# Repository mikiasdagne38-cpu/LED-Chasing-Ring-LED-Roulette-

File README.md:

# LED-Chasing-Ring-LED-Roulette-
This circuit makes a ring of LEDs light up one by one in a fast circle, creating a "chasing" or running light effect. It is a classic hobbyist project used for decorative lights, games, or electronic roulette.

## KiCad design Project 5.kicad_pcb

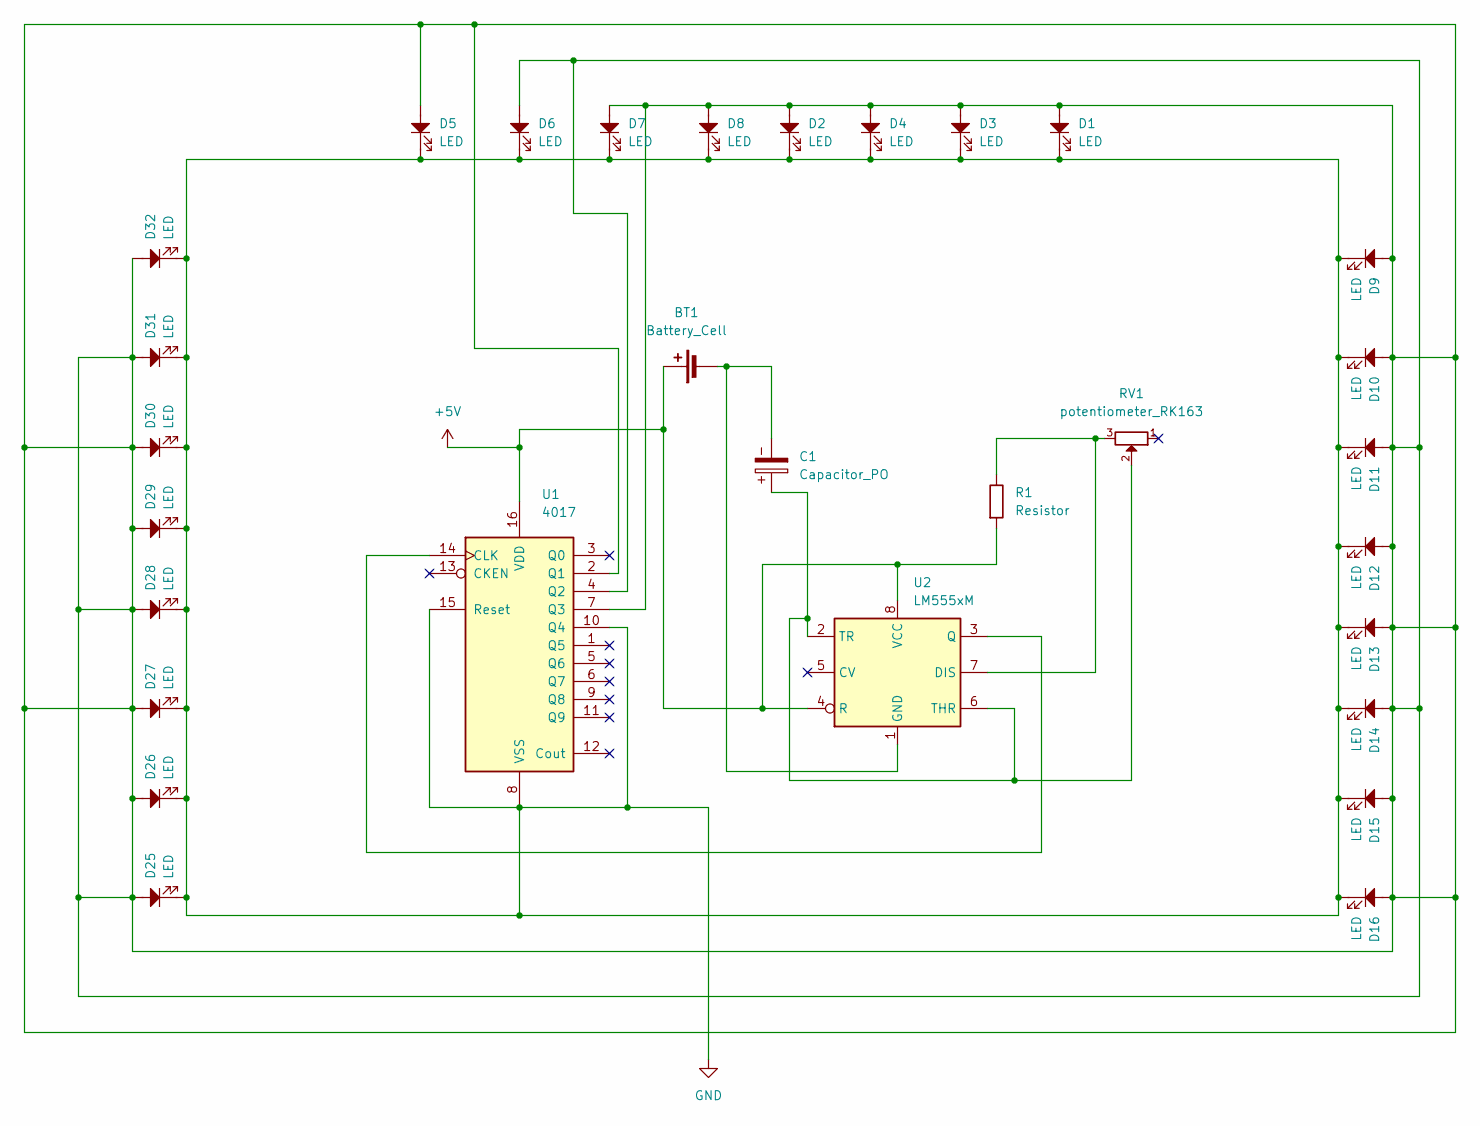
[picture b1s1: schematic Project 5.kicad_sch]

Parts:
BT1: Battery_Cell; TerminalBlock_Xinya_XY308-2.54-2P_1x02_P2.54mm_Horizontal
C1: Capacitor_PO; CP_Radial_D5.0mm_P2.50mm
D1, D2, D3, D4, D5, D6, D7, D8, D9, D10, D11, D12, D13, D14, D15, D16, D25, D26, D27, D28, D29, D30, D31, D32: LED; LED_D5.0mm
R1: Resistor; R_Axial_DIN0207_L6.3mm_D2.5mm_P10.16mm_Horizontal
RV1: potentiometer_RK163; TRIM_3296W-1-250
U1: 4017; DIP794W45P254L1969H508Q16
U2: LM555xM; SOIC-8_3.9x4.9mm_P1.27mm

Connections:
+5V: BT1.1 (+), R1.1, U1.16 (VDD), U2.4 (R), U2.8 (VCC)
GND: D1.1, D2.1, D3.1, D4.1, D5.1, D6.1, D7.1, D8.1, D9.1, D10.1, D11.1, D12.1, D13.1, D14.1, D15.1, D16.1, D25.1, D26.1, D27.1, D28.1, D29.1, D30.1, D31.1, D32.1, U1.8 (VSS), U1.10 (Q4), U1.15 (Reset)
unnamed: BT1.2 (-), C1.2, U2.1 (GND)
unnamed: U1.14 (CLK), U2.3 (Q)
unnamed: D1.2, D2.2, D3.2, D4.2, D5.2, D6.2, D7.2, D8.2, D9.2, D10.2, D11.2, D12.2, D13.2, D14.2, D15.2, D16.2, D25.2, D26.2, D27.2, D28.2, D29.2, D30.2, D31.2, D32.2, U1.2 (Q1), U1.4 (Q2), U1.7 (Q3)
unnamed: R1.2, RV1.3, U2.7 (DIS)
unnamed: C1.1, RV1.2, U2.2 (TR), U2.6 (THR)

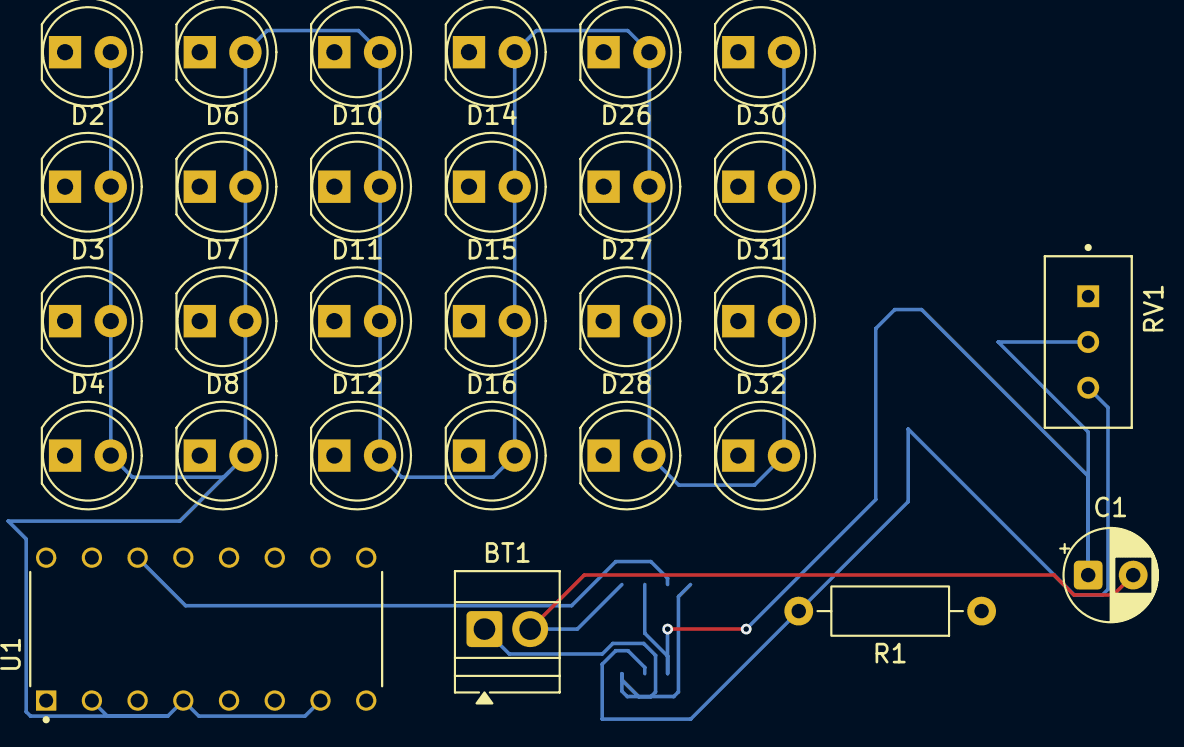
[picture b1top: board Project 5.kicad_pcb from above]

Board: 4 copper layers, 30 parts (1 on the bottom side), 7 nets.
